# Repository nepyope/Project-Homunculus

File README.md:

# Project Homunculus

Project Homunculus is open-source, low-cost hardware for capturing human hand and arm motions. It has two parts. The first is a Hall-effect VR glove that tracks finger joints with magnetic sensors instead of cameras or external tracking stations. The second is a 7-DOF exoskeleton arm for whole-body teleoperation. Together they let you drive dexterous hands and humanoids directly from your own body, so you can collect demonstration data for robot learning without motion-capture rigs or expensive commercial gloves.

The glove is built from off-the-shelf parts (SS49E Hall sensors, an ESP32-C3, a 16-channel multiplexer) and costs under $20 in materials.  Everything is included so you can build, modify, and extend it yourself: firmware, a 3D-printable enclosure, the PCB design, and a Unity visualizer. 

## Repository layout

| Path | Description |
|------|-------------|
| [`glove/`](glove/) | **Hall Effect VR Glove** — firmware, 3D-printable enclosure, PCB design, Unity hand visualizer, and experimental tools. |
| [`exo/`](exo/) | **Exoskeleton Arm** *(submodule)* — 7-DOF whole-body control device with CAD, firmware, URDF models, and PCB files. |

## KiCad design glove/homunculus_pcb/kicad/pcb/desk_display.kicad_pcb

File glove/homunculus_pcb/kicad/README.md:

# PCB Desk Display

The idea was to have a special purpose, small footprint PCB for connecting an I²C Display, Button and Status LED.

## The PCB

The PCB including the ESP32-C3 Antenna has a total footprint of `20mmx30mm`. The files can be found in [`./pcb`](./pcb).

## The Code

The code currently is only a small placeholder to test the different parts of the PCB. The files can be found in [`./code`](./code) in form of a PlatformIO project.

## License

Enjoy the work and do what you want. `CERN OHL v2 Permissive`

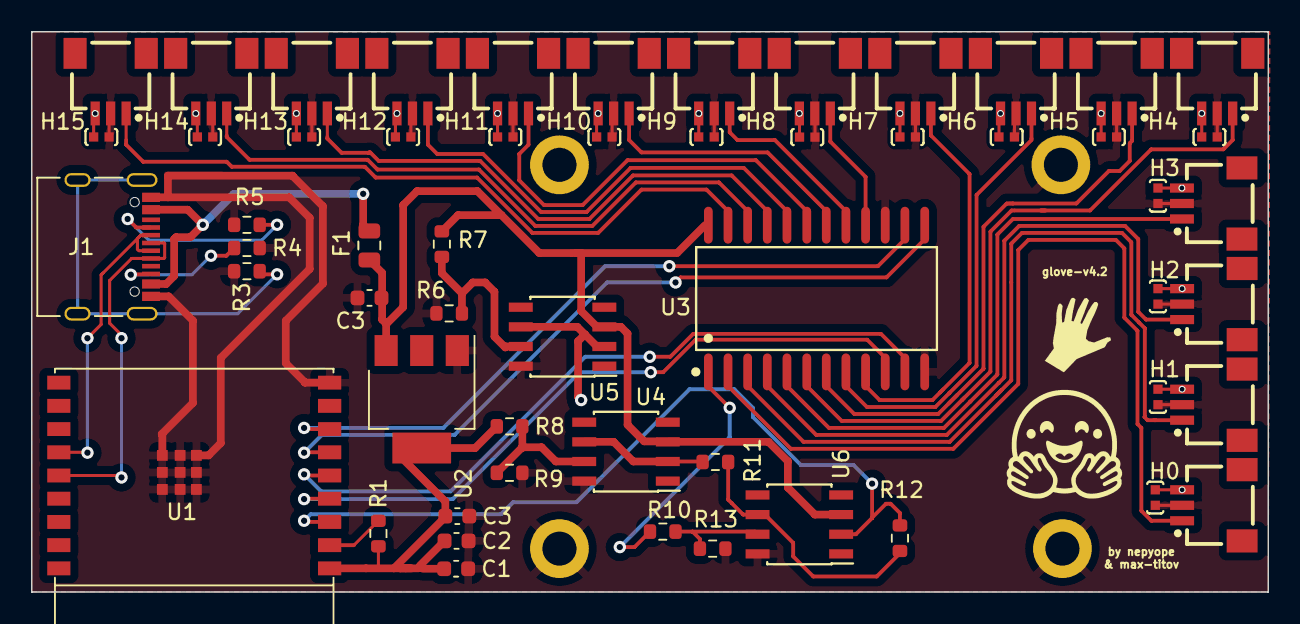
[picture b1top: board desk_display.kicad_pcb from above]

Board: 2 copper layers, 79.9 x 36.2 mm, 56 parts (0 on the bottom side), 34 nets.

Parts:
C0, C1, C1#2, C1#3, C1#4, C1#5, C1#6, C1#7, C1#8, C1#9, C1#11, C1#12, C1#13, C2#2, C3, C9: C-0402-0.1uF-16V; C0402
C1#10, C2, C3#2, C3#3: 10µF; C_0603_1608Metric
F1: Fuse_0805_2012Metric
H0, H1, H2, H3, H4, H5, H6, H7, H8, H9, H10, H11, H12, H13, H14, H15: JST-SM03B; CONN-SMD_SM03B-SRSS-TB-LF-SN-P
J1: USB_C_Receptacle_USB2.0; USB_C_Receptacle_Palconn_UTC16-G
R1, R4, R5, R6: 5.11K; R_0603_1608Metric
R3: 1M; R_0603_1608Metric
R7: 1K; R_0603_1608Metric
R8, R10, R10#2, R11, R12: 10K; R_0603_1608Metric
R9: 2.4K; R_0603_1608Metric
U1: ESP32-C3-WROOM-02
U2: AMS1117-3.3; SOT-223-3_TabPin2
U3: CD74HC4067M96; SOIC-24_L15.4-W7.5-P1.27-LS10.3-BL
U4, U5, U6: OPA340UA; SOIC-8_3.9x4.9mm_Pitch1.27mm

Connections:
+0.6V: R8.2, R9.1, R11.1, U4.2, U4.6, U4.7
+3.3V: C1#10.1, C2.1, C3#3.1, R1.1, R8.1, U1.1 (3V3), U2.2 (VO)
+4.2V: C0.2, C1.2, C1#2.2, C1#4.2, C1#5.2, C1#6.2, C1#7.2, C1#8.2, C1#9.2, C1#11.2, C1#12.2, C1#13.2, C2#2.2, C3.2, C9.2, H0.3, H1.3, H2.3, H3.1 (3), H4.3, H5.3, H6.3, H7.3, H8.3, H9.3, H10.3, H11.3, H12.1 (3), H13.3, H14.3, H15.3, R6.1, R7.2, U5.2, U5.6, U5.7
+5VD: C3#2.1, F1.1, F1.2, J1.A4 (VBUS), J1.A9 (VBUS), J1.B4 (VBUS), J1.B9 (VBUS), R7.1, U2.3 (VI), U3.24 (VCC), U4.3, U5.3, U6.3
D+: J1.A6 (D+), J1.B6 (D+), U1.14 (GPIO19/USB_D+)
D-: J1.A7 (D-), J1.B7 (D-), U1.13 (GPIO18/USB_D-)
EN: R1.2, U1.2 (EN/CHIP_PU)
GND: C0.1, C1.1, C1#2.1, C1#3.1, C1#4.1, C1#5.1, C1#6.1, C1#7.1, C1#8.1, C1#9.1, C1#10.2, C1#11.1, C1#12.1, C1#13.1, C2.2, C2#2.1, C3.1, C3#2.2, C3#3.2, C9.1, H0.2, H1.2, H2.2, H3.2, H4.2, H5.2, H6.2, H7.2, H8.2, H9.2, H10.2, H11.2, H12.2, H13.2, H14.2, H15.2, J1.A1 (GND), J1.A12 (GND), J1.B1 (GND), J1.B12 (GND), R3.2, R4.2, R5.2, R6.2, R9.2, R10.2, U1.9 (GND), U1.19 (GND), U2.1 (GND), U3.12 (GND), U3.15 (~E), U4.8, U5.8, U6.8
H*: R11.2, R12.1, R12.2, U1.3 (GPIO4/ADC1_CH4), U6.2, U6.6
HALL_0: H0.1, U3.2 (I7)
HALL_1: H1.1, U3.3 (I6)
HALL_2: H2.1, U3.4 (I5)
HALL_3: H3.1, U3.5 (I4)
HALL_4: H4.1, U3.6 (I3)
HALL_5: H5.1, U3.7 (I2)
HALL_6: H6.1, U3.8 (I1)
HALL_7: H7.1, U3.9 (I0)
HALL_8: H8.1, U3.16 (I15)
HALL_9: H9.1, U3.17 (I14)
HALL_10: H10.1, U3.18 (I13)
HALL_11: H11.1, U3.19 (I12)
HALL_12: H12.1, U3.20 (I11)
HALL_13: H13.1, U3.21 (I10)
HALL_14: H14.1, U3.22 (I9)
HALL_15: H15.1, U3.23 (I8)
MUX_OUT: R10.1, R10#2.1, R10#2.2, U3.1 (COMMONINPUT/OUTPUT), U6.7
NC: U4.1, U4.4, U5.4, U6.1, U6.4
unnamed: J1.A5 (CC1), R5.1
unnamed: J1.B5 (CC2), R4.1
unnamed: J1.S1 (SHIELD), R3.1
S0: U1.4 (GPIO5/ADC2_CH0), U3.10 (S0)
S1: U1.5 (GPIO6), U3.11 (S1)
S2: U1.6 (GPIO7), U3.13 (S3)
S3: U1.7 (GPIO8), U3.14 (S2)

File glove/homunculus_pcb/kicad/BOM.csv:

Designator,Footprint,Quantity,Value,LCSC Part #
"C0, C1_13, C1_12, C1_11, C1_10, C1_9, C1_8, C1_7, C1_6, C1_5, C1_3, C1_2, C1, C2, C3_3, C9",C0402,16,C-0402-0.1uF-16V,C1525
"C1_4, C2_2, C3_2, C3",0603,4,10µF,
F1,0805,1,Fuse_0805_2012Metric,
"H0, H1, H10, H11, H12, H13, H14, H15, H2, H3, H4, H5, H6, H7, H8, H9",CONN-SMD_SM03B-SRSS-TB-LF-SN-P,16,JST-SM03B,C160403
J1,USB_C_Receptacle_Palconn_UTC16-G,1,USB_C_Receptacle_USB2.0,
"R1, R4, R5",0603,3,5.11K,
R3,0603,1,1M,
U1,ESP32-C3-WROOM-02,1,ESP32-C3-WROOM-02,
U2,SOT-223-3_TabPin2,1,AMS1117-3.3,
U3,SOIC-24_L15.4-W7.5-P1.27-LS10.3-BL,1,CD74HC4067M96,C496123

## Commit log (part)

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2024-01-01 new stuff
2024-08-06 added visualizer
2024-08-06 meta files
2024-08-06 readme
2024-09-18 test
2024-09-18 added unity project for hand visualizer
2024-09-18 fix readme
2024-09-18 add stls
2025-02-20 add yt and dc
2025-02-24 break stl into individual MCP DIP PIP IP
2025-02-24 add base
2025-02-24 added readme
2025-02-24 link to max's pcb
2025-02-24 add correct enclosure
2025-02-25 use m2 nuts instead of threaded inserts for m2 base (ty robertdalesmith)
2025-09-22 Add files via upload
    add glove tutorial draft
2026-05-12 Create firmware.ino
    add firmware
2026-05-12 refactor
2026-05-12 add html visualizer
